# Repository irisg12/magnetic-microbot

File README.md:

# magnetic-microrobot

Magnetic microrobot manipulation system that adapts a flex PCB platform inspired by the Hackaday “2D Stepper Motor Etched on PCB” project.

## Overview

This repository contains code, schematics, and CAD files for a mm-scale magnetic robot control platform designed for open and closed loop trajectory execution, computer vision robot tracking, and micromanipulation.

The system uses a two-layer flex PCB with orthogonal serpentine traces powered by two stepper motor drivers. The resulting configuration generates magnetic fields that allow a mm-scale magnet placed on the PCB to be manipulated in 8 directions. 

## Features 

- Live tracking of robot and obstacle positions for closed-loop control and image processing
- Direction control and motor driver actuation via Arduino serial communication
- MATLAB A* pathfinding algorithm and visualization for trajectory planning and obstacle avoidance 

### Included Files

- FLEX PCB Gerber Files for manufacturing
- DXF file for acrylic base with cutouts for PCB mounting and wiring
- STL files for obstacles and manipulation payloads 

## Requirements

- MATLAB Support Package for USB Webcams
- MATLAB Image Processing Toolbox

## File Organization

- Upload microbot_multidirection_serial.ino to Arduino Uno

## Hardware Components 

- Flex PCB with stiffener
- N52 disk magnets: 1mm x 0.5mm (4 ct) and 3mm x 1mm (1 ct)
- Arduino Uno
- 170 pin breadboard
- A4988 Stepper Motor Drivers (2 ct)
- 3/16" thick acrylic sheet: each base has approximate dimensions 4.2" x 5.9" 
- M3 nuts and bolts for mounting 
- Webcam & webcam stand

## Wiring Schematic
Default pin connections for Arduino, motor drivers, and PCB also available in SetupSchematic.svg. Drivers are full-stepping, which results in the smoothest motion.

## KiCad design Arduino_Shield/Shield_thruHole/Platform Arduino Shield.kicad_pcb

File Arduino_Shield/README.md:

# Arduino shield for platform system

This folder contains relevant files for an Arduino motor shield to control each platform.

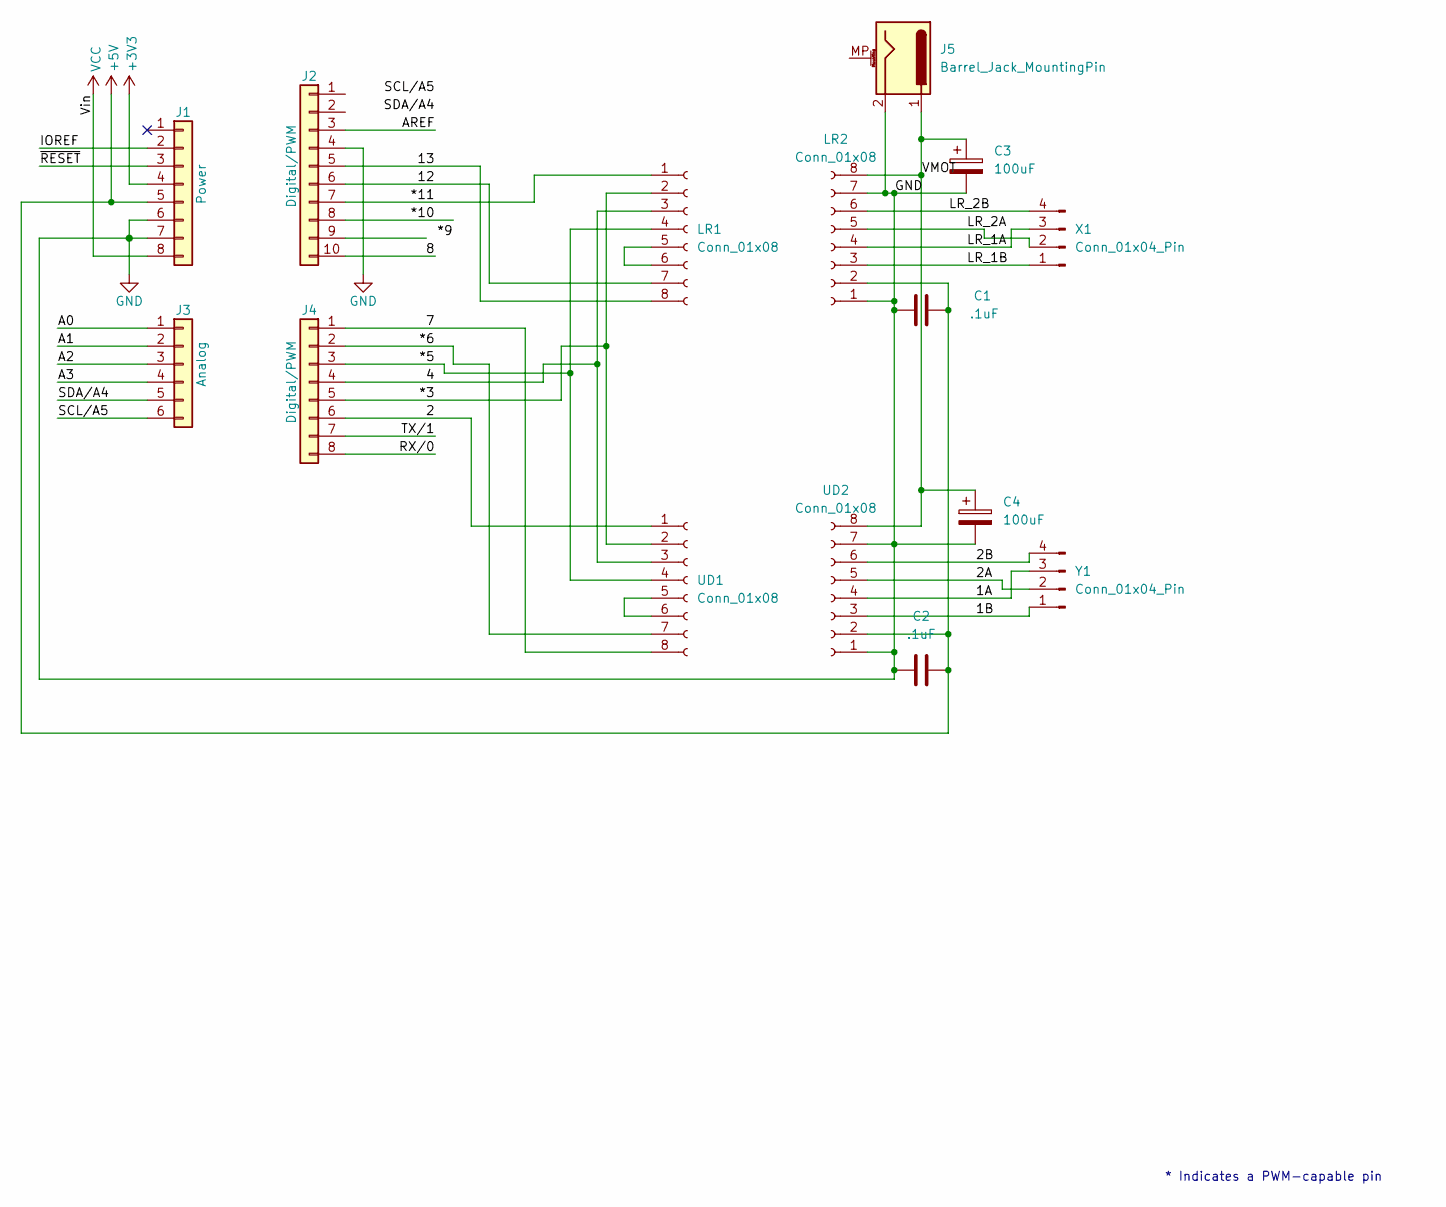
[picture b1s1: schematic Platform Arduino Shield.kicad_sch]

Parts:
C1, C2: .1uF; C_Disc_D5.0mm_W2.5mm_P5.00mm
C3, C4: 100uF; CP_Radial_D6.3mm_P2.50mm
J1: Power; PinSocket_1x08_P2.54mm_Vertical
J2: Digital/PWM; PinSocket_1x10_P2.54mm_Vertical
J3: Analog; PinSocket_1x06_P2.54mm_Vertical
J4: Digital/PWM; PinSocket_1x08_P2.54mm_Vertical
J5: Barrel_Jack_MountingPin; BarrelJack_Horizontal
LR1, LR2: Conn_01x08; PinSocket_1x08_P2.54mm_Vertical
UD1, UD2: Conn_01x08; PinSocket_1x08_P2.54mm_Vertical
X1: Conn_01x04_Pin; PinHeader_1x04_P2.54mm_Vertical
Y1: Conn_01x04_Pin; PinHeader_1x04_P2.54mm_Vertical

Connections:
+3V3: J1.4
+5V: C1.2, C2.2, J1.5, LR2.2, UD2.2
/1A: UD2.4, Y1.3
/1B: UD2.3, Y1.1
/2: J4.6, UD1.1
/2A: UD2.5, Y1.2
/2B: UD2.6, Y1.4
/4: J4.4, LR1.3, UD1.3
/7: J4.1, UD1.8
/8: J2.10
/12: J2.6, LR1.7
/13: J2.5, LR1.8
/*3: J4.5, LR1.2, UD1.2
/*5: J4.3, LR1.4, UD1.4
/*6: J4.2, UD1.7
/*10: J2.8
/*11: J2.7, LR1.1
/A0: J3.1
/A1: J3.2
/A2: J3.3
/A3: J3.4
/AREF: J2.3
/IOREF: J1.2
/LR_1A: LR2.4, X1.3
/LR_1B: LR2.3, X1.1
/LR_2A: LR2.5, X1.2
/LR_2B: LR2.6, X1.4
/RX/0: J4.8
/SCL/A5: J3.6
/SDA/A4: J3.5
/TX/1: J4.7
/VMOT: C3.1, C4.1, J5.1, LR2.8, UD2.8
/~RESET: J1.3
GND: C1.1, C2.1, C3.2, C4.2, J1.6, J1.7, J2.4, J5.2, LR2.1, LR2.7, UD2.1, UD2.7
unnamed: LR1.5, LR1.6
unnamed: UD1.5, UD1.6
VCC: J1.8

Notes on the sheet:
* Indicates a PWM-capable pin

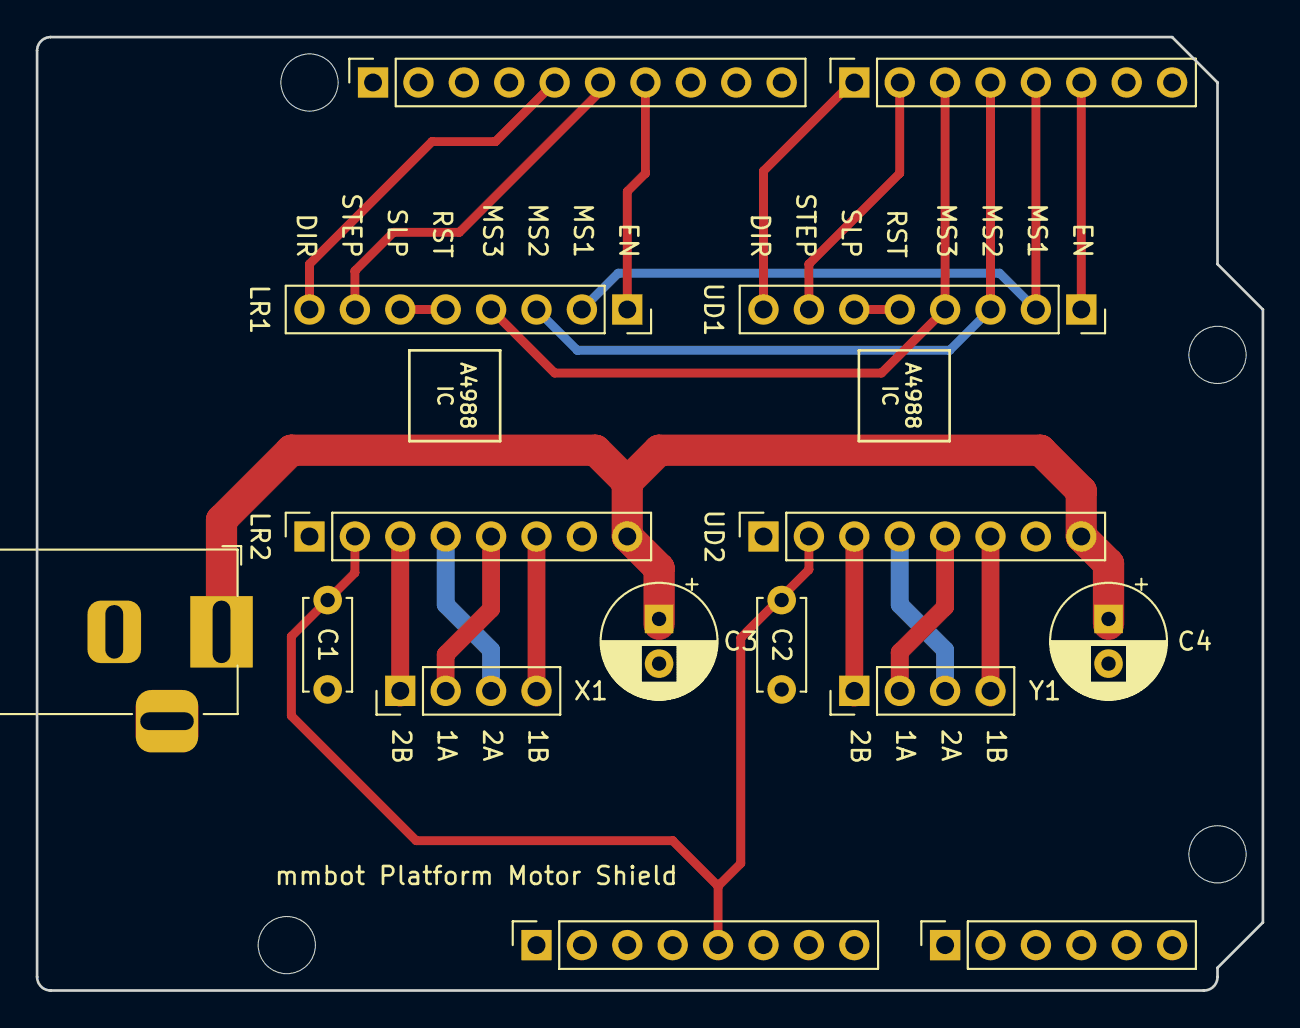
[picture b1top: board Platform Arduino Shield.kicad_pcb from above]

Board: 2 copper layers, 68.6 x 53.3 mm, 19 parts (0 on the bottom side), 22 nets.

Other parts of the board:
MH1, MH2, MH3, MH4: MountingHole_3.2mm

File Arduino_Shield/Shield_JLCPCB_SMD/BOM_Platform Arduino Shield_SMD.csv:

"Id";"Designator";"Footprint";"Quantity";"Designation";"Supplier and ref";
1;"C4,C3";"C_1206_3216Metric";2;"100uF";;;
2;"J1";"PinSocket_1x08_P2.54mm_Vertical";1;"Power";;;
3;"J3";"PinSocket_1x06_P2.54mm_Vertical";1;"Analog";;;
4;"J2";"PinSocket_1x10_P2.54mm_Vertical";1;"Digital/PWM";;;
5;"J4";"PinSocket_1x08_P2.54mm_Vertical";1;"Digital/PWM";;;
6;"C1,C2";"C_0805_2012Metric";2;".1uF";;;
7;"J5";"BarrelJack_Horizontal";1;"Barrel_Jack_MountingPin";;;
8;"LR1,LR2,UD2,UD1";"PinSocket_1x08_P2.54mm_Vertical";4;"Conn_01x08";;;
9;"X1,Y1";"PinHeader_1x04_P2.54mm_Vertical";2;"Conn_01x04_Pin";;;

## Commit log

2025-01-15 Rename TeamImage1.jpg to MATLAB/TeamImage1.jpg
2025-01-15 Rename TeamImage2.png to MATLAB/TeamImage2.png
2025-01-15 Rename TeamImage3.jpg to MATLAB/TeamImage3.jpg
2025-01-15 Rename ControlGUI.mlapp to MATLAB/ControlGUI.mlapp
2025-01-15 Rename microbot_multidirection_nonserial_v1.ino to Arduino/microbot_multidirection_nonserial_v1/microbot_multidirection_nonserial_v1.ino
2025-01-15 Rename microbot_multidirection_nonserial_v2.ino to Arduino/microbot_multidirection_nonserial_v2/microbot_multidirection_nonserial_v2.ino
2025-01-15 Rename microbot_multidirection_serial.ino to Arduino/microbot_multidirection_serial/microbot_multidirection_serial.ino
2025-04-23 Add files via upload
    File upload for acrylic mounting board and obstacles
2025-04-23 Uploaded wiring schematic
2025-04-23 updated code comments
2025-04-23 rename
2025-04-23 added schematic
2025-04-23 Update code comments
2025-04-30 organized CAD files and updated Arduino code
2025-04-30 Comment 7x7 processing code
2026-05-08 upload shield files
